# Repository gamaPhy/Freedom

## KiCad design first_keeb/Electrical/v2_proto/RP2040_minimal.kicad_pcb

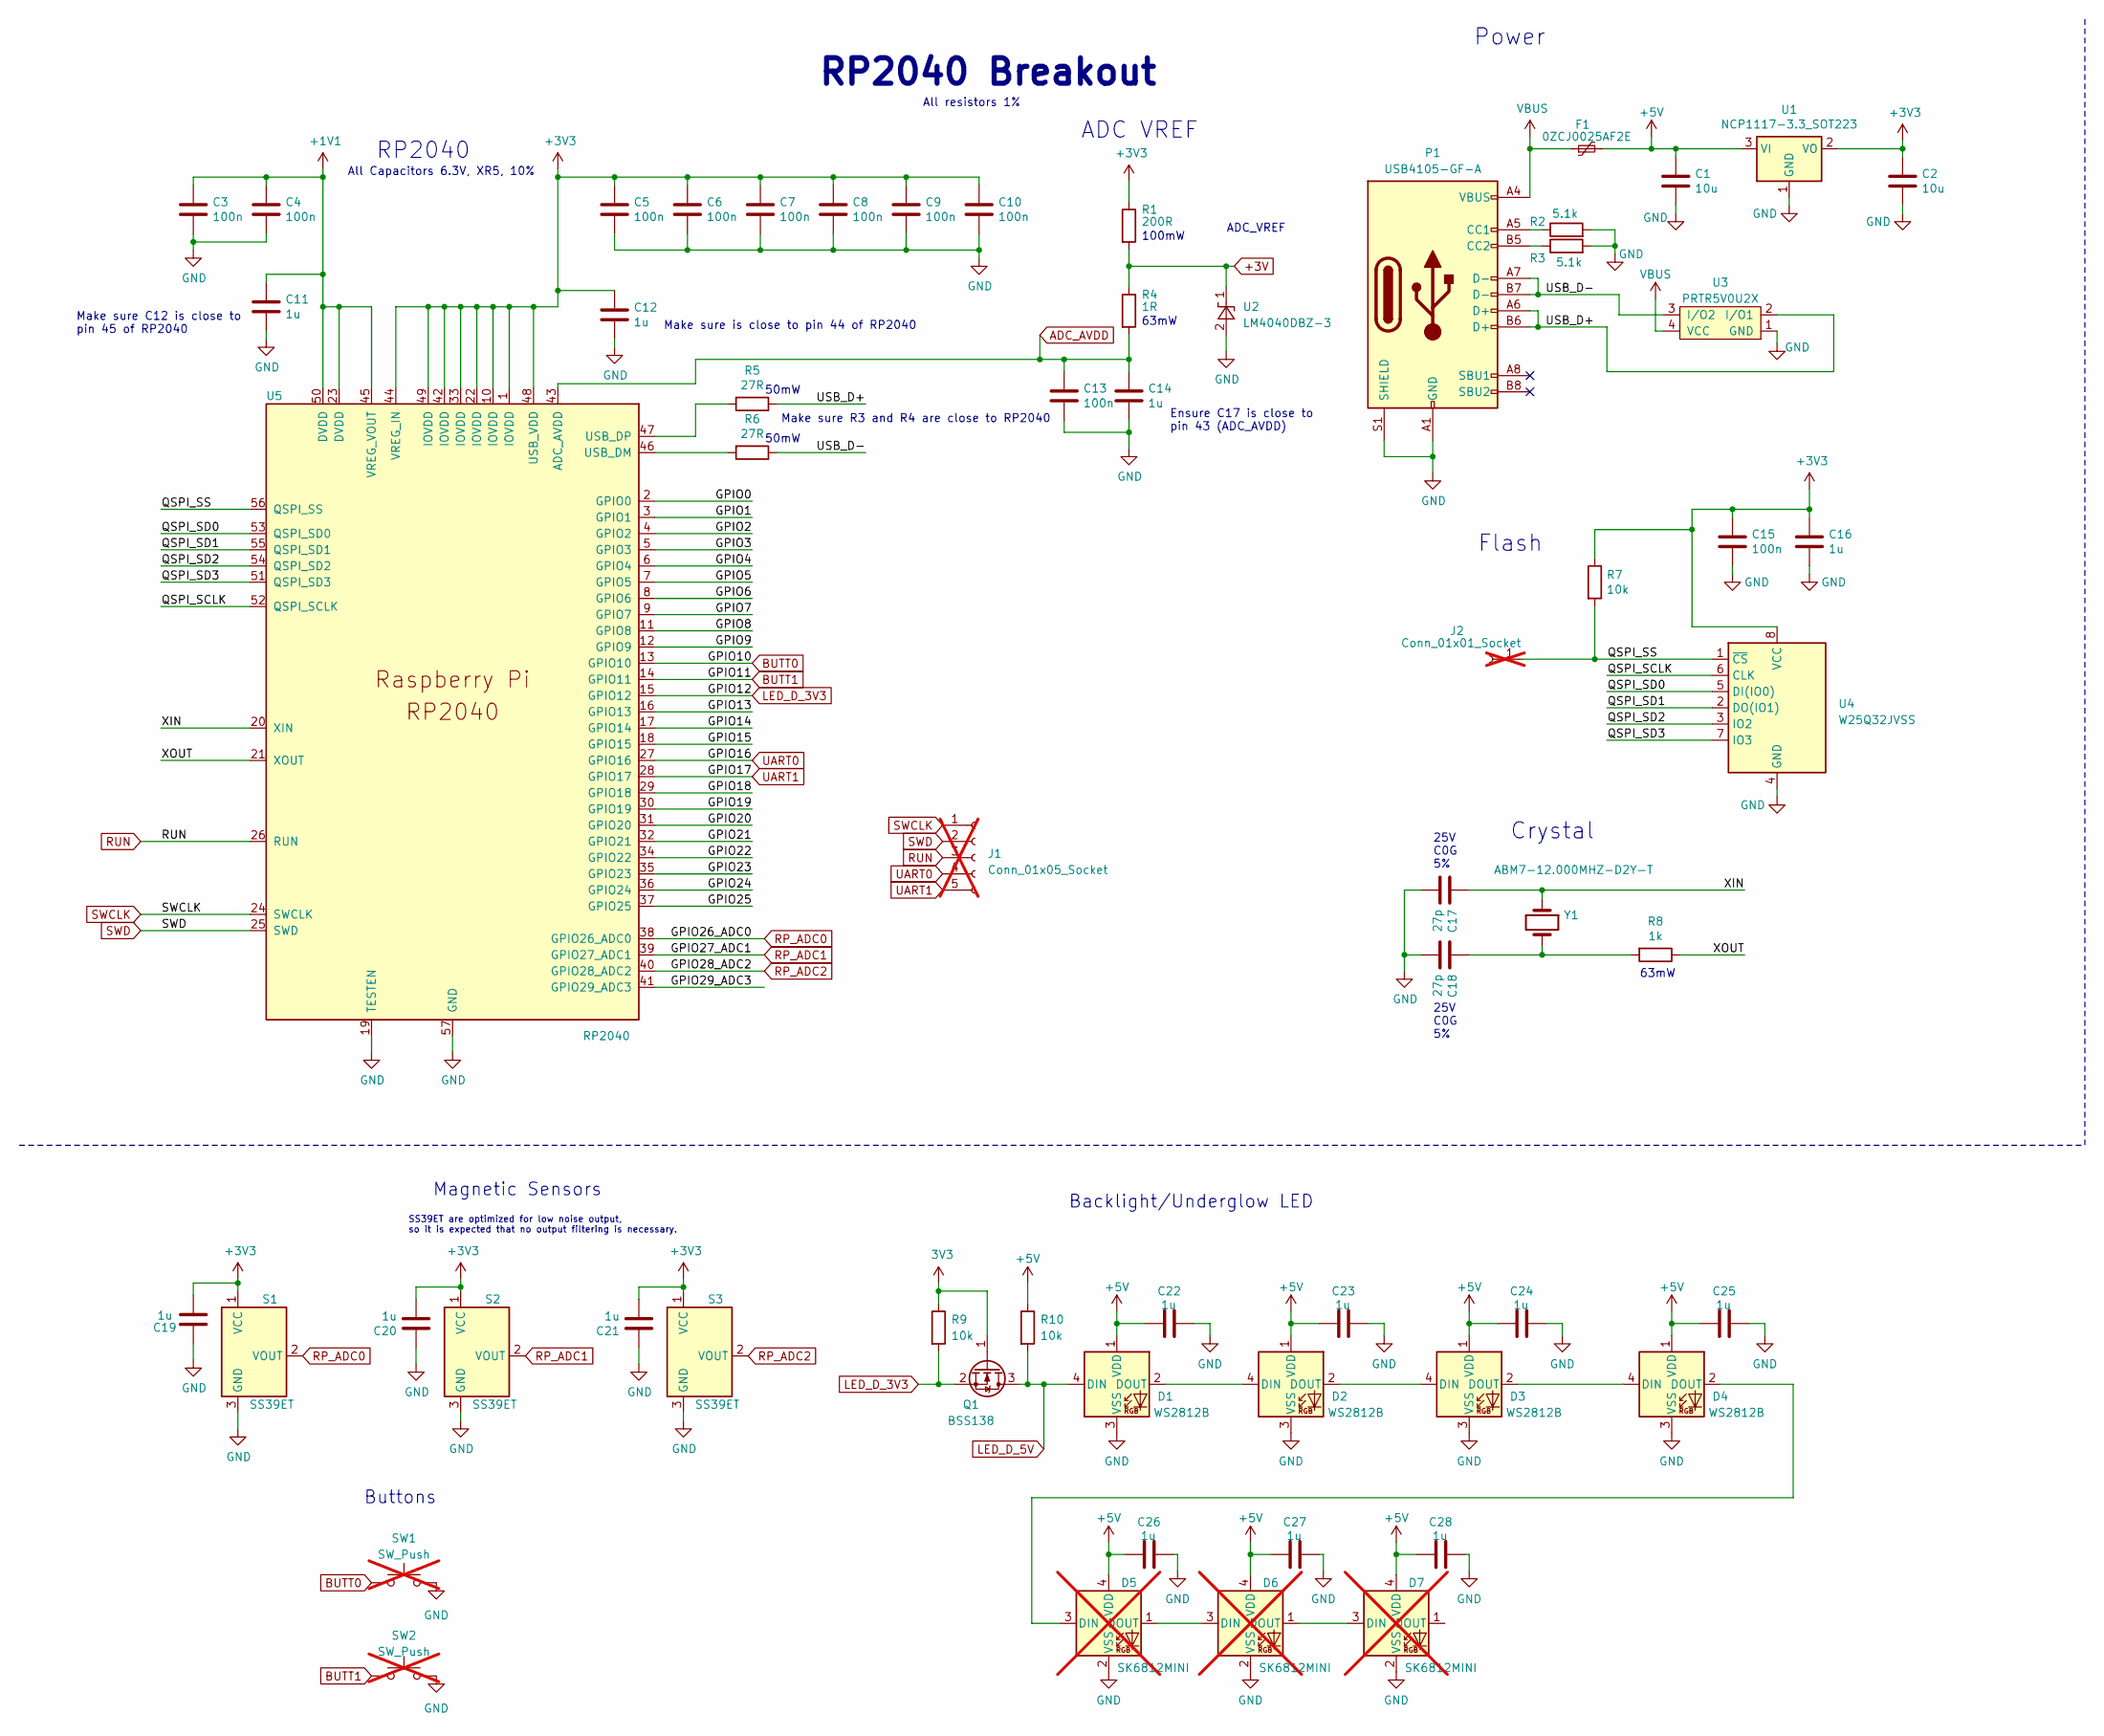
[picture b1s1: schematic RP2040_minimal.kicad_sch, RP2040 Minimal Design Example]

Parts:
C1, C2: 10u; C_0805_2012Metric
C3, C4, C5, C6, C7, C8, C9, C10, C13, C15: 100n; C_0402_1005Metric
C11, C12, C14, C16, C19, C20, C21, C22, C23, C24, C25, C26, C27, C28: 1u; C_0402_1005Metric
C17, C18: 27p; C_0402_1005Metric
D1, D2, D3, D4: WS2812B; LED_WS2812B_PLCC4_5.0x5.0mm_P3.2mm
D5, D6, D7: SK6812MINI; LED_SK6812MINI_PLCC4_3.5x3.5mm_P1.75mm; not fitted
F1: 0ZCJ0025AF2E; Fuse_1206_3216Metric
J1: Conn_01x05_Socket; PinSocket_1x05_P2.54mm_Vertical; not fitted
J2: Conn_01x01_Socket; PinSocket_1x01_P2.54mm_Vertical; not fitted
P1: USB4105-GF-A; USB_C_Receptacle_GCT_USB4105-xx-A_16P_TopMnt_Horizontal
Q1: BSS138; SOT-23
R1: 200R; C_0603_1608Metric
R2, R3: 5.1k; C_0402_1005Metric
R4: 1R; C_0603_1608Metric
R5, R6: 27R; C_0402_1005Metric
R7, R9, R10: 10k; C_0402_1005Metric
R8: 1k; C_0402_1005Metric
S1, S2, S3: SS39ET; SOT-23-3
SW1, SW2: SW_Push; 2-1825027-0_Right_Angle_Button; not fitted
U1: NCP1117-3.3_SOT223; SOT-223-3_TabPin2
U2: LM4040DBZ-3; SOT-23
U3: PRTR5V0U2X; SOT-143
U4: W25Q32JVSS; SOIC-8_5.23x5.23mm_P1.27mm
U5: RP2040; RP2040-QFN-56
Y1: ABM7-12.000MHZ-D2Y-T; Crystal_SMD_Abracon_ABM7-2Pin_6.0x3.5mm

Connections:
+1V1: C3.1, C4.1, C11.1, U5.23 (DVDD), U5.45 (VREG_VOUT), U5.50 (DVDD)
+3V: R1.2, R4.1, U2.1 (K)
+5V: C1.1, C22.1, C23.1, C24.1, C25.1, C26.1, C27.1, C28.1, D1.1 (VDD), D2.1 (VDD), D3.1 (VDD), D4.1 (VDD), D5.4 (VDD), D6.4 (VDD), D7.4 (VDD), F1.2, R10.1, U1.3 (VI)
/GPIO0: U5.2 (GPIO0)
/GPIO1: U5.3 (GPIO1)
/GPIO2: U5.4 (GPIO2)
/GPIO3: U5.5 (GPIO3)
/GPIO4: U5.6 (GPIO4)
/GPIO5: U5.7 (GPIO5)
/GPIO6: U5.8 (GPIO6)
/GPIO7: U5.9 (GPIO7)
/GPIO8: U5.11 (GPIO8)
/GPIO9: U5.12 (GPIO9)
/GPIO13: U5.16 (GPIO13)
/GPIO14: U5.17 (GPIO14)
/GPIO15: U5.18 (GPIO15)
/GPIO18: U5.29 (GPIO18)
/GPIO19: U5.30 (GPIO19)
/GPIO20: U5.31 (GPIO20)
/GPIO21: U5.32 (GPIO21)
/GPIO22: U5.34 (GPIO22)
/GPIO23: U5.35 (GPIO23)
/GPIO24: U5.36 (GPIO24)
/GPIO25: U5.37 (GPIO25)
/GPIO29_ADC3: U5.41 (GPIO29_ADC3)
/QSPI_SCLK: U4.6 (CLK), U5.52 (QSPI_SCLK)
/QSPI_SD0: U4.5 (DI(IO0)), U5.53 (QSPI_SD0)
/QSPI_SD1: U4.2 (DO(IO1)), U5.55 (QSPI_SD1)
/QSPI_SD2: U4.3 (IO2), U5.54 (QSPI_SD2)
/QSPI_SD3: U4.7 (IO3), U5.51 (QSPI_SD3)
/QSPI_SS: J2.1, R7.2, U4.1 (~CS), U5.56 (QSPI_SS)
/USB_D+: P1.A6 (D+), P1.B6 (D+), R5.1, U3.2 (I/O1)
/USB_D-: P1.A7 (D-), P1.B7 (D-), R6.1, U3.3 (I/O2)
/XIN: C17.1, U5.20 (XIN), Y1.1
/XOUT: R8.1, U5.21 (XOUT)
ADC_AVDD: C13.1, C14.1, R4.2, U5.43 (ADC_AVDD)
BUTT0: SW1.1, U5.13 (GPIO10)
BUTT1: SW2.1, U5.14 (GPIO11)
GND: C1.2, C2.2, C3.2, C4.2, C5.2, C6.2, C7.2, C8.2, C9.2, C10.2, C11.2, C12.2, C13.2, C14.2, C15.2, C16.2, C17.2, C18.2, C19.1, C20.1, C21.1, C22.2, C23.2, C24.2, C25.2, C26.2, C27.2, C28.2, D1.3 (VSS), D2.3 (VSS), D3.3 (VSS), D4.3 (VSS), D5.2 (VSS), D6.2 (VSS), D7.2 (VSS), P1.A1 (GND), P1.A12 (GND), P1.B1 (GND), P1.B12 (GND), P1.S1 (SHIELD), R2.2, R3.2, S1.3 (GND), S2.3 (GND), S3.3 (GND), SW1.2, SW2.2, U1.1 (GND), U2.2 (A), U3.1 (GND), U4.4 (GND), U5.19 (TESTEN), U5.57 (GND)
LED_D_3V3: Q1.2 (S), R9.2, U5.15 (GPIO12)
LED_D_5V: D1.4 (DIN), Q1.3 (D), R10.2
unnamed: C18.1, R8.2, Y1.2
unnamed: D1.2 (DOUT), D2.4 (DIN)
unnamed: D2.2 (DOUT), D3.4 (DIN)
unnamed: D3.2 (DOUT), D4.4 (DIN)
unnamed: D4.2 (DOUT), D5.3 (DIN)
unnamed: D5.1 (DOUT), D6.3 (DIN)
unnamed: D6.1 (DOUT), D7.3 (DIN)
unnamed: P1.A5 (CC1), R2.1
unnamed: P1.B5 (CC2), R3.1
unnamed: R6.2, U5.46 (USB_DM)
unnamed: R5.2, U5.47 (USB_DP)
RP_ADC0: S1.2 (VOUT), U5.38 (GPIO26_ADC0)
RP_ADC1: S2.2 (VOUT), U5.39 (GPIO27_ADC1)
RP_ADC2: S3.2 (VOUT), U5.40 (GPIO28_ADC2)
RUN: J1.3, U5.26 (RUN)
SWCLK: J1.1, U5.24 (SWCLK)
SWD: J1.2, U5.25 (SWD)
UART0: J1.4, U5.27 (GPIO16)
UART1: J1.5, U5.28 (GPIO17)
VBUS: F1.1, P1.A4 (VBUS), P1.A9 (VBUS), P1.B4 (VBUS), P1.B9 (VBUS), U3.4 (VCC)

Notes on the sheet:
RP2040 Breakout
All Capacitors 6.3V, XR5, 10%
Make sure C12 is close to pin 45 of RP2040
ADC VREF
63mW
25V C0G 5%
ADC_VREF
Make sure R3 and R4 are close to RP2040
Magnetic Sensors
Backlight/Underglow LED
RP2040
SS39ET are optimized for low noise output, so it is expected that no output filtering is necessary.
Power
Buttons
Crystal
Make sure is close to pin 44 of RP2040
All resistors 1%
50mW
Flash
Ensure C17 is close to pin 43 (ADC_AVDD)
100mW

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
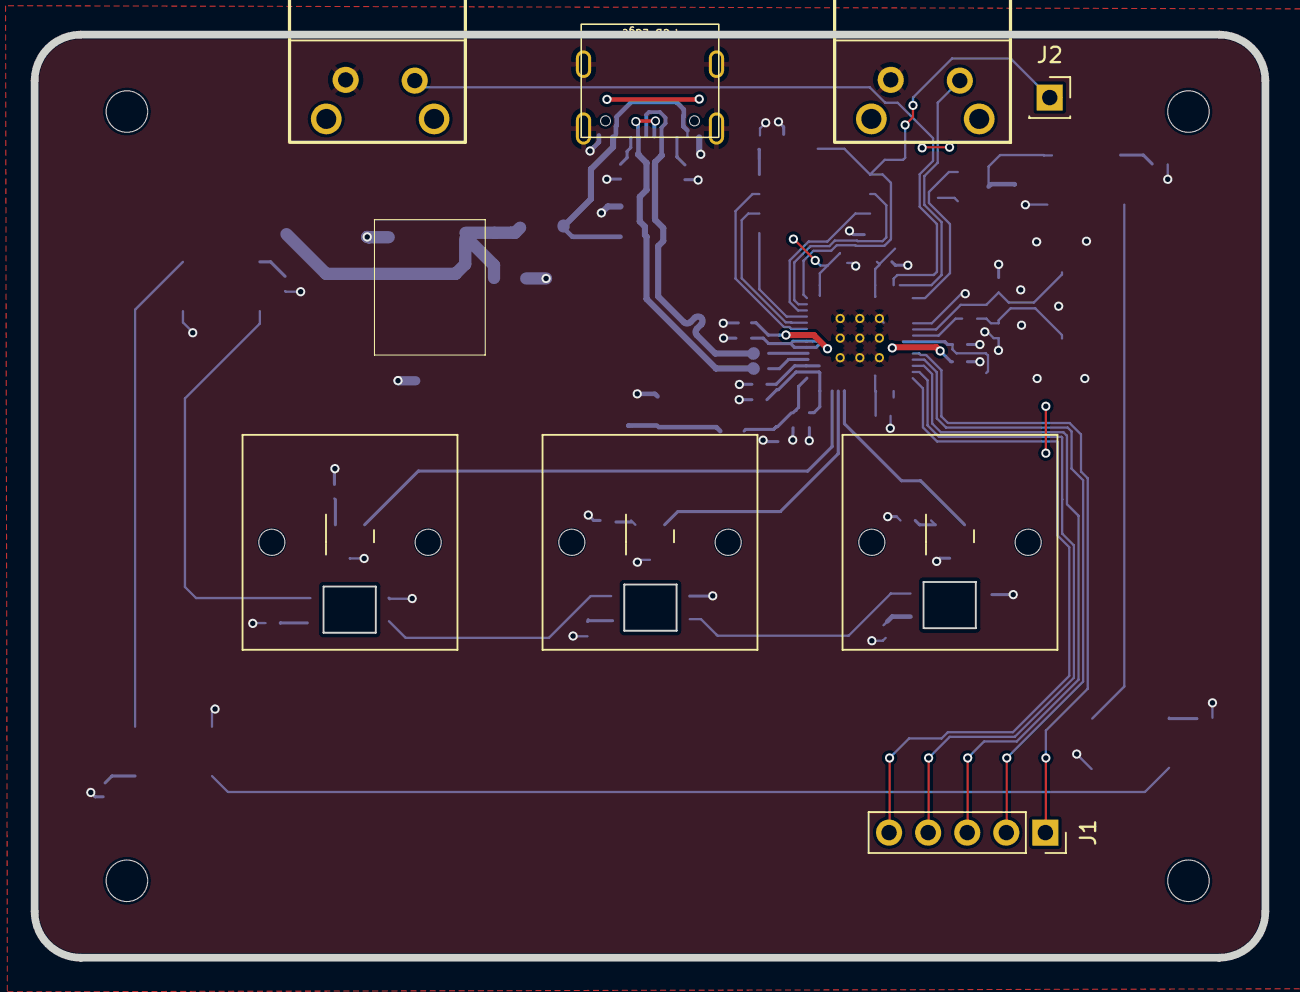
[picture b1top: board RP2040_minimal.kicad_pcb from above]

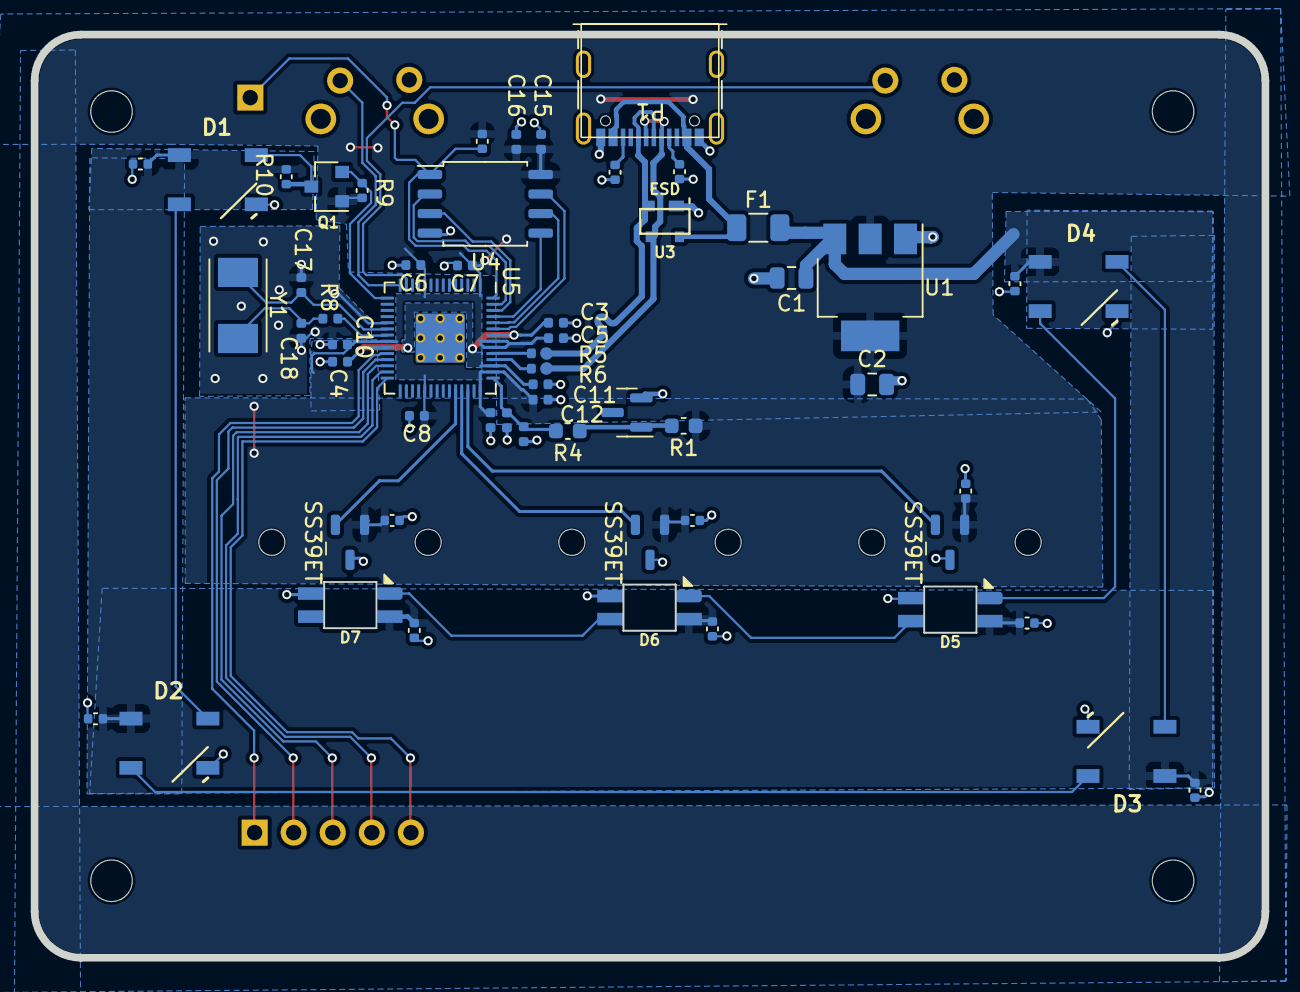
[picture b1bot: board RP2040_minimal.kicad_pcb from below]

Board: 2 copper layers, 80.0 x 60.0 mm, 61 parts (57 on the bottom side), 40 nets.

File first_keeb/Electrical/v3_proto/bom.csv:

"Comment All resistor at least 1%, and >=100mW All capacitor at least 5%, and >= 6.3 V ",Designator,Footprint
10uF,"C1, C2",Capacitor_SMD:C_0805_2012Metric
100nF,"C3, C4, C5, C6, C7, C8, C9, C10, C13, C15",Capacitor_SMD:C_0402_1005Metric
1uF,"C11, C12, C14, C16, C19, C20, C21, C22, C23, C24, C25, C26, C27, C28",Capacitor_SMD:C_0402_1005Metric
27pF,"C17, C18",Capacitor_SMD:C_0402_1005Metric
WS2812B,"D1, D2, D3, D4",LED_SMD:LED_WS2812B_PLCC4_5.0x5.0mm_P3.2mm
0ZCJ0025AF2E,F1,Fuse:Fuse_1206_3216Metric
USB4105-GF-A,P1,Connector_USB:USB_C_Receptacle_GCT_USB4105-xx-A_16P_TopMnt_Horizontal
BSS138,Q1,Package_TO_SOT_SMD:SOT-23
200 Ohm,R1,Capacitor_SMD:C_0603_1608Metric
5.1k,"R2, R3",Capacitor_SMD:C_0402_1005Metric
1 Ohm,R4,Capacitor_SMD:C_0603_1608Metric
27 Ohm ,"R5, R6",Capacitor_SMD:C_0402_1005Metric
10k,"R7, R9, R10",Capacitor_SMD:C_0402_1005Metric
1k,R8,Capacitor_SMD:C_0402_1005Metric
SS39ET,"S1, S2, S3",Package_TO_SOT_SMD:SOT-23-3
NCP1117-3.3_SOT223,U1,Package_TO_SOT_SMD:SOT-223-3_TabPin2
LM4040DBZ-3,U2,Package_TO_SOT_SMD:SOT-23
PRTR5V0U2X,U3,Package_TO_SOT_SMD:SOT-143
W25Q32JVSS,U4,Package_SO:SOIC-8_5.23x5.23mm_P1.27mm
RP2040,U5,RP2040_minimal:RP2040-QFN-56
ABM7-12.000MHZ-D2Y-T,Y1,Crystal:Crystal_SMD_Abracon_ABM7-2Pin_6.0x3.5mm
